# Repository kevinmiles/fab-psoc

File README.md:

fab-psoc
========

Easy to mill development board for PSoC 4

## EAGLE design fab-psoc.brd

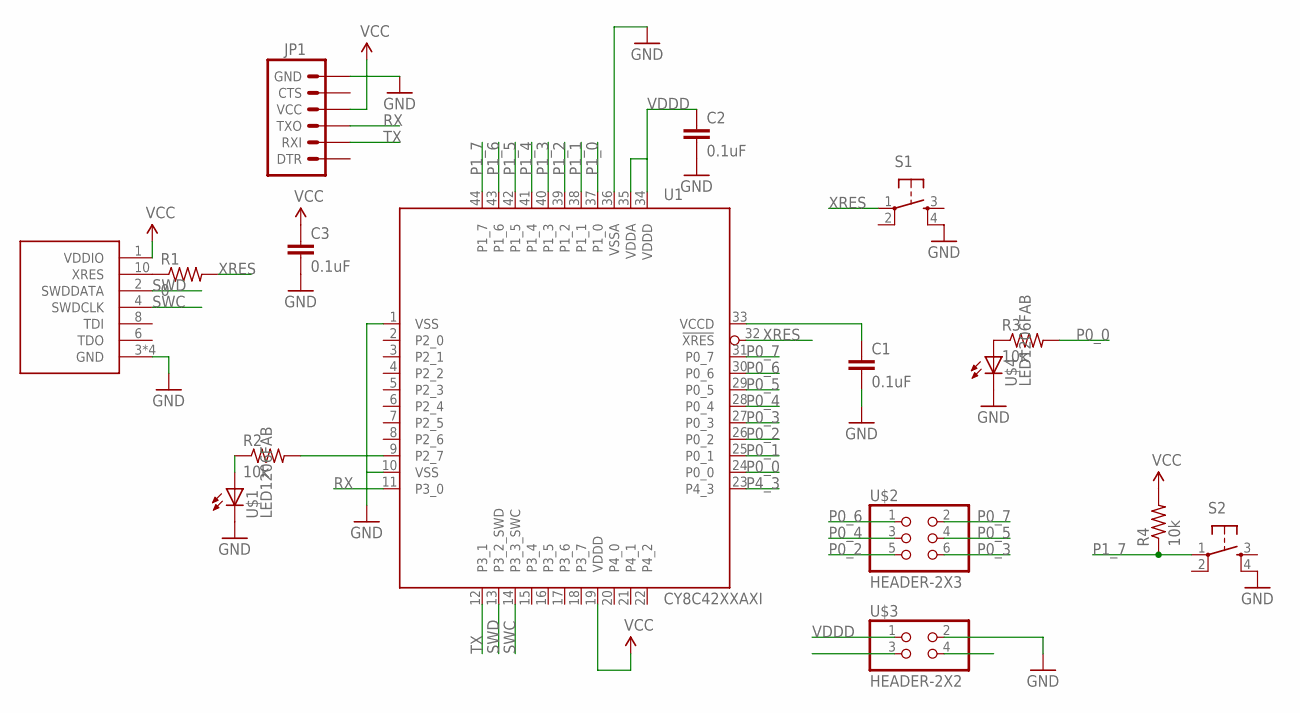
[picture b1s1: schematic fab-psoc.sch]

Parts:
C1, C2, C3: 0.1uF; C1206FAB
JP1: FTDI-SMD
MINIPROG3: MINIPROG; 2X5SMD
R1: 0; R1206FAB
R2, R3, R4: 10k; R1206FAB
S1, S2: SWITCH
U1: CY8C42XXAXI; TQFP-10X10-44
U$1, U$4: LED1206FAB; R1206FAB
U$2: HEADER-2X3; 2X3SMD
U$3: HEADER-2X2; 2X2SMD

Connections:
GND: C1.2, C2.2, C3.2, JP1.6 (GND), MINIPROG3.3 (GND), MINIPROG3.5 (GND), MINIPROG3.7 (GND), MINIPROG3.9 (GND), S1.4 (S1), S2.4 (S1), U1.1 (VSS), U1.10 (VSS), U1.36 (VSSA), U$1.2 (C), U$3.2, U$4.2 (C)
unnamed: C1.1, U1.33 (VCCD)
unnamed: MINIPROG3.10 (XRES), R1.1
unnamed: R3.1, U$4.1 (A)
unnamed: R2.2, U1.9 (P2_7)
unnamed: R2.1, U$1.1 (A)
P0_0: R3.2, U1.24 (P0_0)
P0_1: U1.25 (P0_1)
P0_2: U1.26 (P0_2), U$2.5
P0_3: U1.27 (P0_3), U$2.6
P0_4: U1.28 (P0_4), U$2.3
P0_5: U1.29 (P0_5), U$2.4
P0_6: U1.30 (P0_6), U$2.1
P0_7: U1.31 (P0_7), U$2.2
P1_0: U1.37 (P1_0)
P1_1: U1.38 (P1_1)
P1_2: U1.39 (P1_2)
P1_3: U1.40 (P1_3)
P1_4: U1.41 (P1_4)
P1_5: U1.42 (P1_5)
P1_6: U1.43 (P1_6)
P1_7: R4.1, S2.1, U1.44 (P1_7)
P2_2: U1.4 (P2_2)
P2_6: U1.8 (P2_6)
P3_6: U1.17 (P3_6)
P4_3: U1.23 (P4_3)
RX: JP1.3 (TXO), U1.11 (P3_0)
SWC: MINIPROG3.4 (SWDCLK), U1.14 (P3_3_SWC)
SWD: MINIPROG3.2 (SWDDATA), U1.13 (P3_2_SWD)
TX: JP1.2 (RXI), U1.12 (P3_1)
VCC: C3.1, JP1.4 (VCC), MINIPROG3.1 (VDDIO), R4.2, U1.19 (VDDD)
VDDD: C2.1, U1.34 (VDDD), U1.35 (VDDA), U$3.1
XRES: R1.2, S1.1, U1.32 (!XRES)

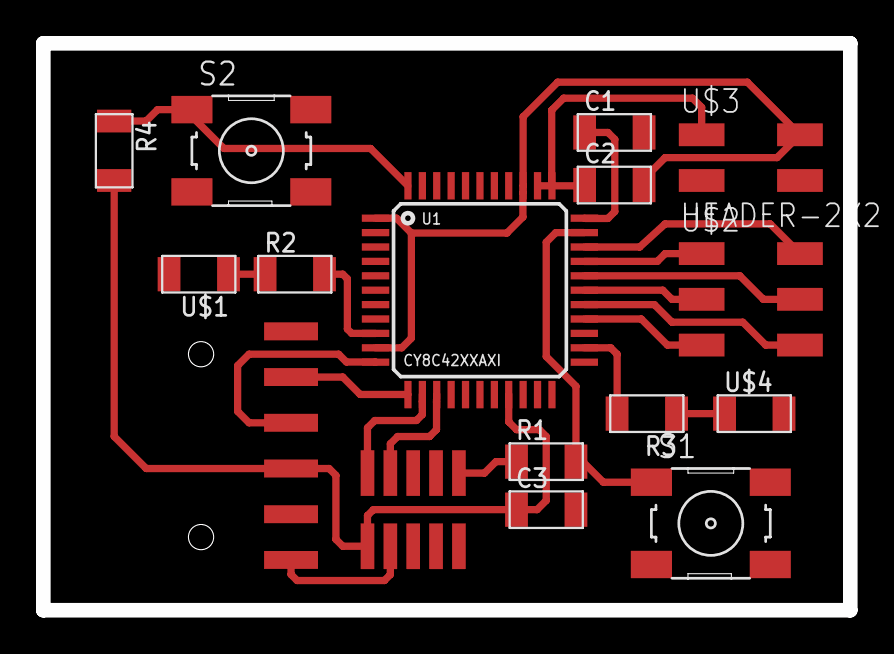
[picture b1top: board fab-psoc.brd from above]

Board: 2 copper layers, 44.8 x 31.5 mm, 16 parts (0 on the bottom side), 21 nets.

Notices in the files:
parts and their libraries:
SparkFun-Aesthetics: Licensing: CC v3.0 Share-Alike You are welcome to use this library for commercial purposes.
